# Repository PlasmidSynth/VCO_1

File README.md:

# VCO_1
Voltage Controlled Oscillator, design 1

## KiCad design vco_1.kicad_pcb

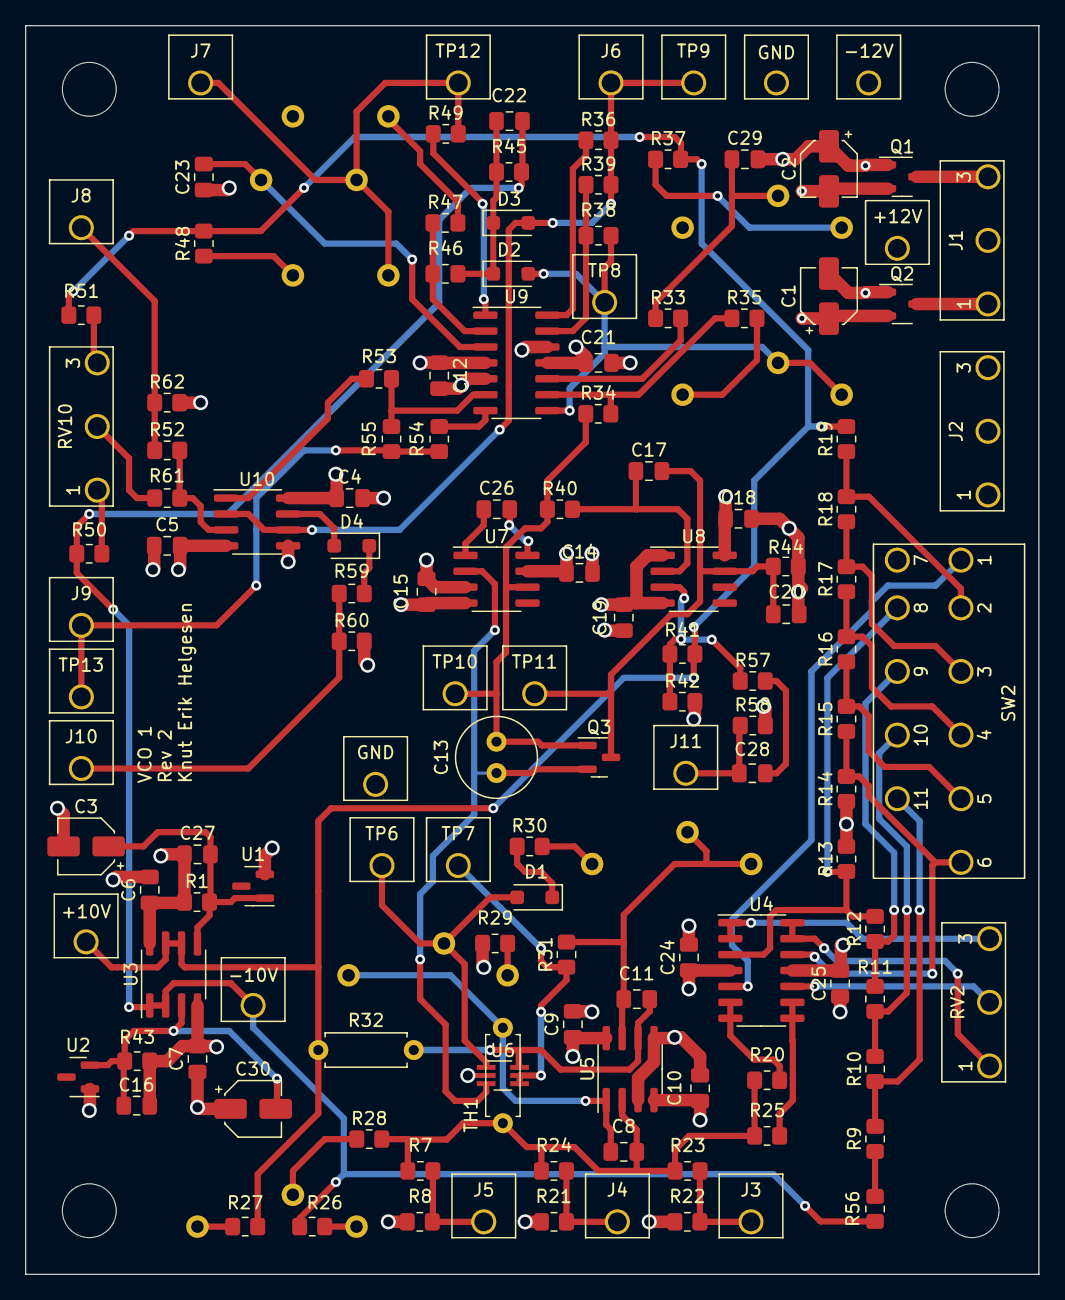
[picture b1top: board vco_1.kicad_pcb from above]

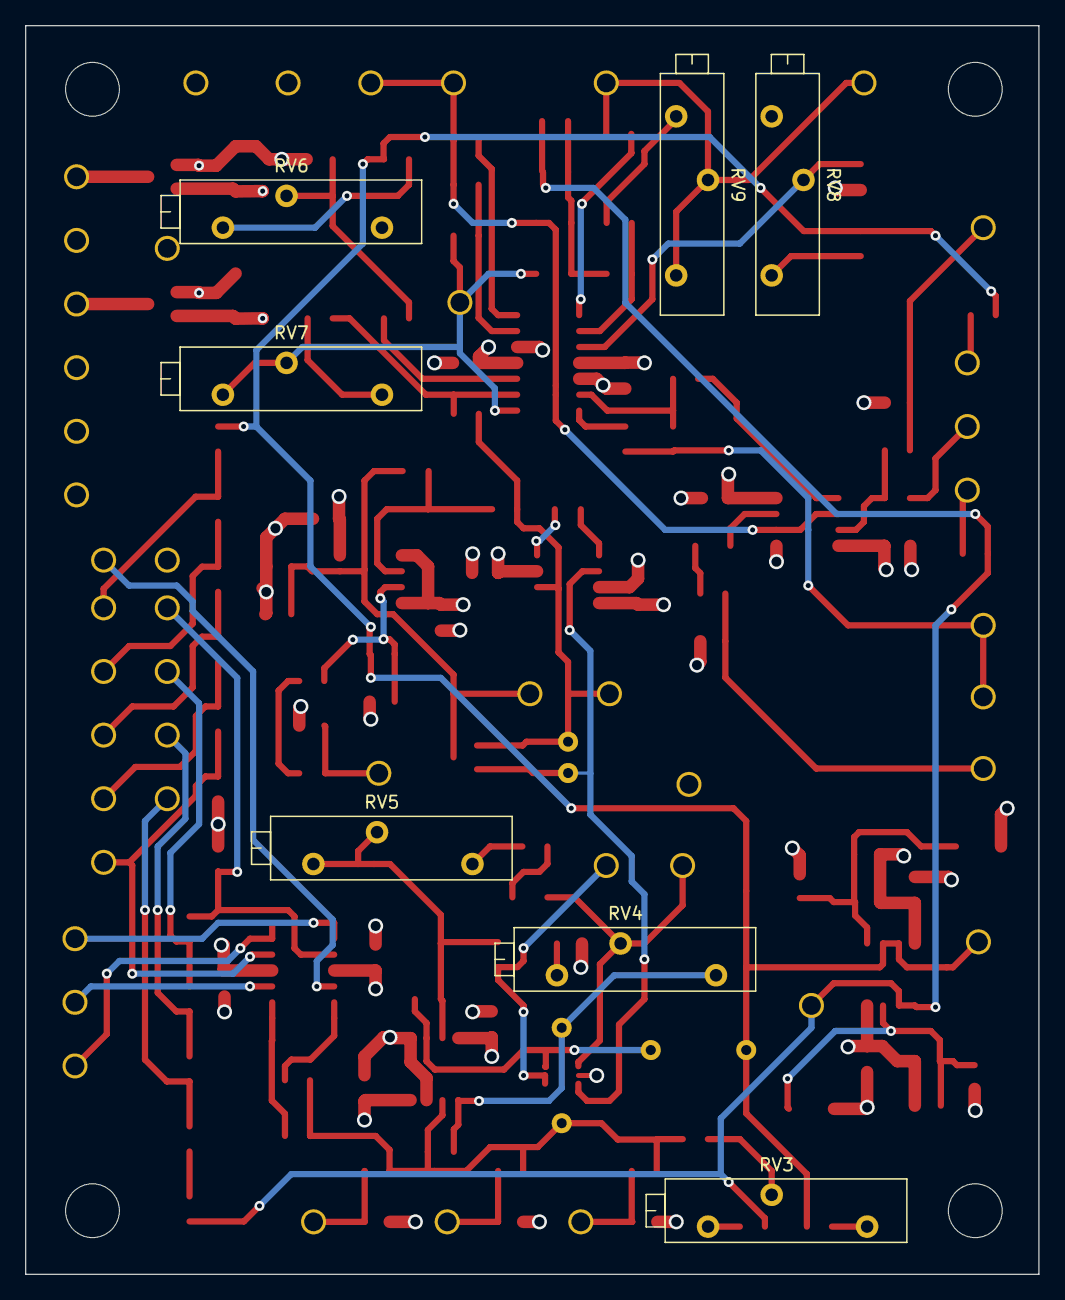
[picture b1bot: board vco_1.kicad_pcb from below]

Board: 4 copper layers, 80.9 x 99.7 mm, 140 parts (7 on the bottom side), 77 nets.

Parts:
C1, C2, C3, C30: 10u; CP_Elec_4x5.4
C4, C5, C6, C7, C9, C10, C12, C14, C15, C16, C18, C19, C21, C22, C23, C24, C25, C27, C29: 0.1u; C_0805_2012Metric_Pad1.18x1.45mm_HandSolder
C8, C11, C20, C26: 100p; C_0805_2012Metric_Pad1.18x1.45mm_HandSolder
C13: 5000p; C_Radial_D6.3mm_H7.0mm_P2.50mm
C17: 33p; C_0805_2012Metric_Pad1.18x1.45mm_HandSolder
C28: 0.001u; C_0805_2012Metric_Pad1.18x1.45mm_HandSolder
D1, D2, D3, D4: 1N914; D_SOD-123F
J1: Power input; Connector_3x1_1.5mm
J2: Daisy chain power; Connector_3x1_1.5mm
J3, J4, J5: CV in; Connector_1x1_1.5mm
J6: saw out; Connector_1x1_1.5mm
J7: tri out; Connector_1x1_1.5mm
J8: Pulse width input; Connector_1x1_1.5mm
J9: pulse out; Connector_1x1_1.5mm
J10: freq out; Connector_1x1_1.5mm
J11: sync in; Connector_1x1_1.5mm
Q1: SQ2348ES; SOT-23-3
Q2: Si2393DS; SOT-23-3
Q3: MMBFJ111; SOT-23
R1, R10, R11, R12, R13, R14, R15, R16, R17, R18, R31, R36, R43, R49, R54, R56, R57: 1k; R_0805_2012Metric_Pad1.20x1.40mm_HandSolder
R7, R8, R20, R21, R22, R23, R24, R25, R28, R52, R58, R61, R62: 100k; R_0805_2012Metric_Pad1.20x1.40mm_HandSolder
R9, R19: 5k; R_0805_2012Metric_Pad1.20x1.40mm_HandSolder
R26, R27, R38, R39, R41, R42, R46, R53, R59: 10k; R_0805_2012Metric_Pad1.20x1.40mm_HandSolder
R29: 470; R_0805_2012Metric_Pad1.20x1.40mm_HandSolder
R30: 4.7k; R_0805_2012Metric_Pad1.20x1.40mm_HandSolder
R32: 4.7M; R_Axial_DIN0207_L6.3mm_D2.5mm_P7.62mm_Horizontal
R33, R34, R35: 5.6k; R_0805_2012Metric_Pad1.20x1.40mm_HandSolder
R37: 18k; R_0805_2012Metric_Pad1.20x1.40mm_HandSolder
R40: 8.2k; R_0805_2012Metric_Pad1.20x1.40mm_HandSolder
R44: 2.2k; R_0805_2012Metric_Pad1.20x1.40mm_HandSolder
R45: 22k; R_0805_2012Metric_Pad1.20x1.40mm_HandSolder
R47: 15k; R_0805_2012Metric_Pad1.20x1.40mm_HandSolder
R48: 12k; R_0805_2012Metric_Pad1.20x1.40mm_HandSolder
R50, R51: 56k; R_0805_2012Metric_Pad1.20x1.40mm_HandSolder
R55: 3.9k; R_0805_2012Metric_Pad1.20x1.40mm_HandSolder
R60: 6.8k; R_0805_2012Metric_Pad1.20x1.40mm_HandSolder
RV2, RV10: 100k; Connector_3x1_1.5mm
RV3, RV6, RV7, RV8, RV9: 10k; Potentiometer_Bourns_3006P_Horizontal
RV4: 100; Potentiometer_Bourns_3006P_Horizontal
RV5: 100k; Potentiometer_Bourns_3006P_Horizontal
SW2: SW_Rotary10; Connector_Octave_Switch_10_pos_1.5mm
TH1: 2k 3300ppm PTC temco; R_Axial_DIN0207_L6.3mm_D2.5mm_P7.62mm_Horizontal
TP1: +12V; Connector_1x1_1.5mm
TP2, TP14: GND; Connector_1x1_1.5mm
TP3: -12V; Connector_1x1_1.5mm
TP4: -10V; Connector_1x1_1.5mm
TP5: +10V; Connector_1x1_1.5mm
TP6: Summed input; Connector_1x1_1.5mm
TP7: Current source voltage; Connector_1x1_1.5mm
TP8: inverted saw; Connector_1x1_1.5mm
TP9: saw output; Connector_1x1_1.5mm
TP10: raw saw; Connector_1x1_1.5mm
TP11: integrator reset pulses; Connector_1x1_1.5mm
TP12: tiangle out; Connector_1x1_1.5mm
TP13: pulse out; Connector_1x1_1.5mm
U1, U2: LM4040DBZ-10; SOT-23
U3: OPA1678; SOIC-8_3.9x4.9mm_P1.27mm
U4, U9: OPA1679; SOIC-14_3.9x8.7mm_P1.27mm
U5: OP275; SOIC-8_3.9x4.9mm_P1.27mm
U6: PMP4201Y; SOT-363_SC-70-6_Handsoldering
U7: CA3140; SOIC-8_3.9x4.9mm_P1.27mm
U8: LM311; SOIC-8_3.9x4.9mm_P1.27mm
U10: TL072; SOIC-8_3.9x4.9mm_P1.27mm

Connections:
+10V: R19.2, R27.2, R32.1, R37.2, R41.1, R48.2, R51.2, TP5.1, U3.6 (-), U3.7
+12V: C1.1, C4.1, C6.1, C9.1, C12.1, C14.1, C18.1, C24.1, C27.1, Q2.2 (S), R1.1, TP1.1, U3.8 (V+), U4.4 (V+), U5.8 (V+), U7.7 (V+), U8.8 (V+), U9.4 (V+), U10.8 (V+)
-10V: C22.1, R26.1, R45.1, R50.2, R56.1, TP4.1, U3.1, U3.2 (-)
-12V: C2.2, C5.2, C7.2, C10.2, C15.1, C16.2, C19.1, C21.2, C25.2, Q1.2 (S), R43.2, TP3.1, U3.4 (V-), U4.11 (V-), U5.4 (V-), U7.4 (V-), U8.1 (GND), U8.4 (V-), U9.11 (V-), U10.4 (V-)
/Core/raw_saw: C13.2, Q3.1 (D), R34.1, R40.1, TP10.1, U7.6
/Core/summed_input: C8.2, RV4.1, TH1.1, U5.1
GND: C1.2, C2.1, C3.2, C4.2, C5.1, C6.2, C7.1, C9.2, C10.1, C12.2, C14.2, C15.2, C18.2, C19.2, C20.2, C21.1, C23.1, C24.2, C25.1, C29.2, C30.1, J1.2, J2.2, Q1.1 (G), Q2.1 (G), R8.2, R13.2, R14.1, R21.2, R22.2, R29.2, R42.2, R44.2, R58.2, R60.2, R62.2, RV6.1, RV8.3, SW2.7, TP2.1, TP14.1, U1.2 (A), U2.1 (K), U5.3 (+), U5.5 (+), U6.2, U7.3 (+), U9.5 (+), U9.12 (+), U10.5 (+)
unnamed: C11.2, R31.2, RV5.2, RV5.3, U5.7
unnamed: C26.1, U7.1 (NULL)
unnamed: C28.1, R57.2
unnamed: C29.1, R33.1, RV6.2
unnamed: D1.2 (A), RV4.2, TP6.1, U6.1
unnamed: D1.1 (K), R30.1
unnamed: D2.2 (A), R38.1, RV7.2, RV7.3, TP8.1, U9.8
unnamed: C22.2, D2.1 (K), D3.1 (K), R45.2, R46.1
unnamed: D3.2 (A), J6.1, R36.2, R39.2, TP9.1, U10.2 (-), U10.6 (-)
unnamed: D4.2 (A), U10.7
unnamed: D4.1 (K), R59.1
unnamed: J1.1, J2.1, Q2.3 (D)
unnamed: J1.3, J2.3, Q1.3 (D)
unnamed: J3.1, R22.1, R23.1
unnamed: J4.1, R21.1, R24.1
unnamed: J5.1, R7.1, R8.1
unnamed: J7.1, R49.2, RV9.1, RV9.2, TP12.1
unnamed: J8.1, R52.1, R62.1
unnamed: J9.1, R54.2, R55.2, TP13.1
unnamed: J10.1, R59.2, R60.1
unnamed: C28.2, J11.1, R58.1
unnamed: C17.2, C20.1, Q3.3 (G), R44.1, TP11.1, U8.7
unnamed: C13.1, Q3.2 (S), U6.3, U7.2 (-)
unnamed: R9.2, R10.1, SW2.11
unnamed: R10.2, R11.1, SW2.10
unnamed: R11.2, R12.1, SW2.9
unnamed: R15.2, R16.1, SW2.5
unnamed: R16.2, R17.1, SW2.4
unnamed: R17.2, R18.1, SW2.3
unnamed: R18.2, R19.1, SW2.2
unnamed: R26.2, RV3.3
unnamed: R27.1, RV3.1
unnamed: R28.1, RV3.2
unnamed: R29.1, RV4.3
unnamed: R30.2, RV5.1
unnamed: R31.1, TP7.1, U6.4, U6.5
unnamed: R35.2, RV7.1
unnamed: R36.1, U9.14
unnamed: R37.1, RV6.3
unnamed: R47.2, RV9.3
unnamed: R48.1, RV8.1
unnamed: R49.1, U9.1
unnamed: R50.1, RV10.1
unnamed: R51.1, RV10.3
unnamed: R53.1, U10.1
unnamed: R54.1, U9.7
unnamed: R9.1, R56.2
unnamed: R61.2, RV10.2
unnamed: C3.1, C27.2, R1.2, U1.1 (K), U3.5 (+)
unnamed: C16.1, C30.2, R43.1, U2.2 (A), U3.3 (+)
unnamed: R12.2, R13.1, SW2.8, U4.3 (+)
unnamed: RV2.3, U4.1, U4.2 (-)
unnamed: SW2.1, U4.5 (+)
unnamed: R20.1, U4.6 (-), U4.7
unnamed: RV2.2, U4.10 (+)
unnamed: R25.1, U4.8, U4.9 (-)
unnamed: R14.2, R15.1, SW2.6, U4.12 (+)
unnamed: RV2.1, U4.13 (-), U4.14
unnamed: C8.1, R7.2, R20.2, R23.2, R24.2, R25.2, R28.2, TH1.2, U5.2 (-)
unnamed: C11.1, R32.2, U5.6 (-), U6.6
unnamed: C26.2, U7.8 (STRB)
unnamed: C17.1, R40.2, U8.2 (+)
unnamed: R41.2, R42.1, R57.1, U8.3 (-)
unnamed: C23.2, RV8.2, U9.3 (+)
unnamed: R46.2, R47.1, U9.2 (-)
unnamed: R53.2, R55.1, U9.6 (-)
unnamed: R33.2, U9.10 (+)
unnamed: R34.2, R35.1, U9.9 (-)
unnamed: R38.2, R39.1, U9.13 (-)
unnamed: R52.2, R61.1, U10.3 (+)

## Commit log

2023-12-27 Initial to GitHub
2024-01-02 Revision 2
